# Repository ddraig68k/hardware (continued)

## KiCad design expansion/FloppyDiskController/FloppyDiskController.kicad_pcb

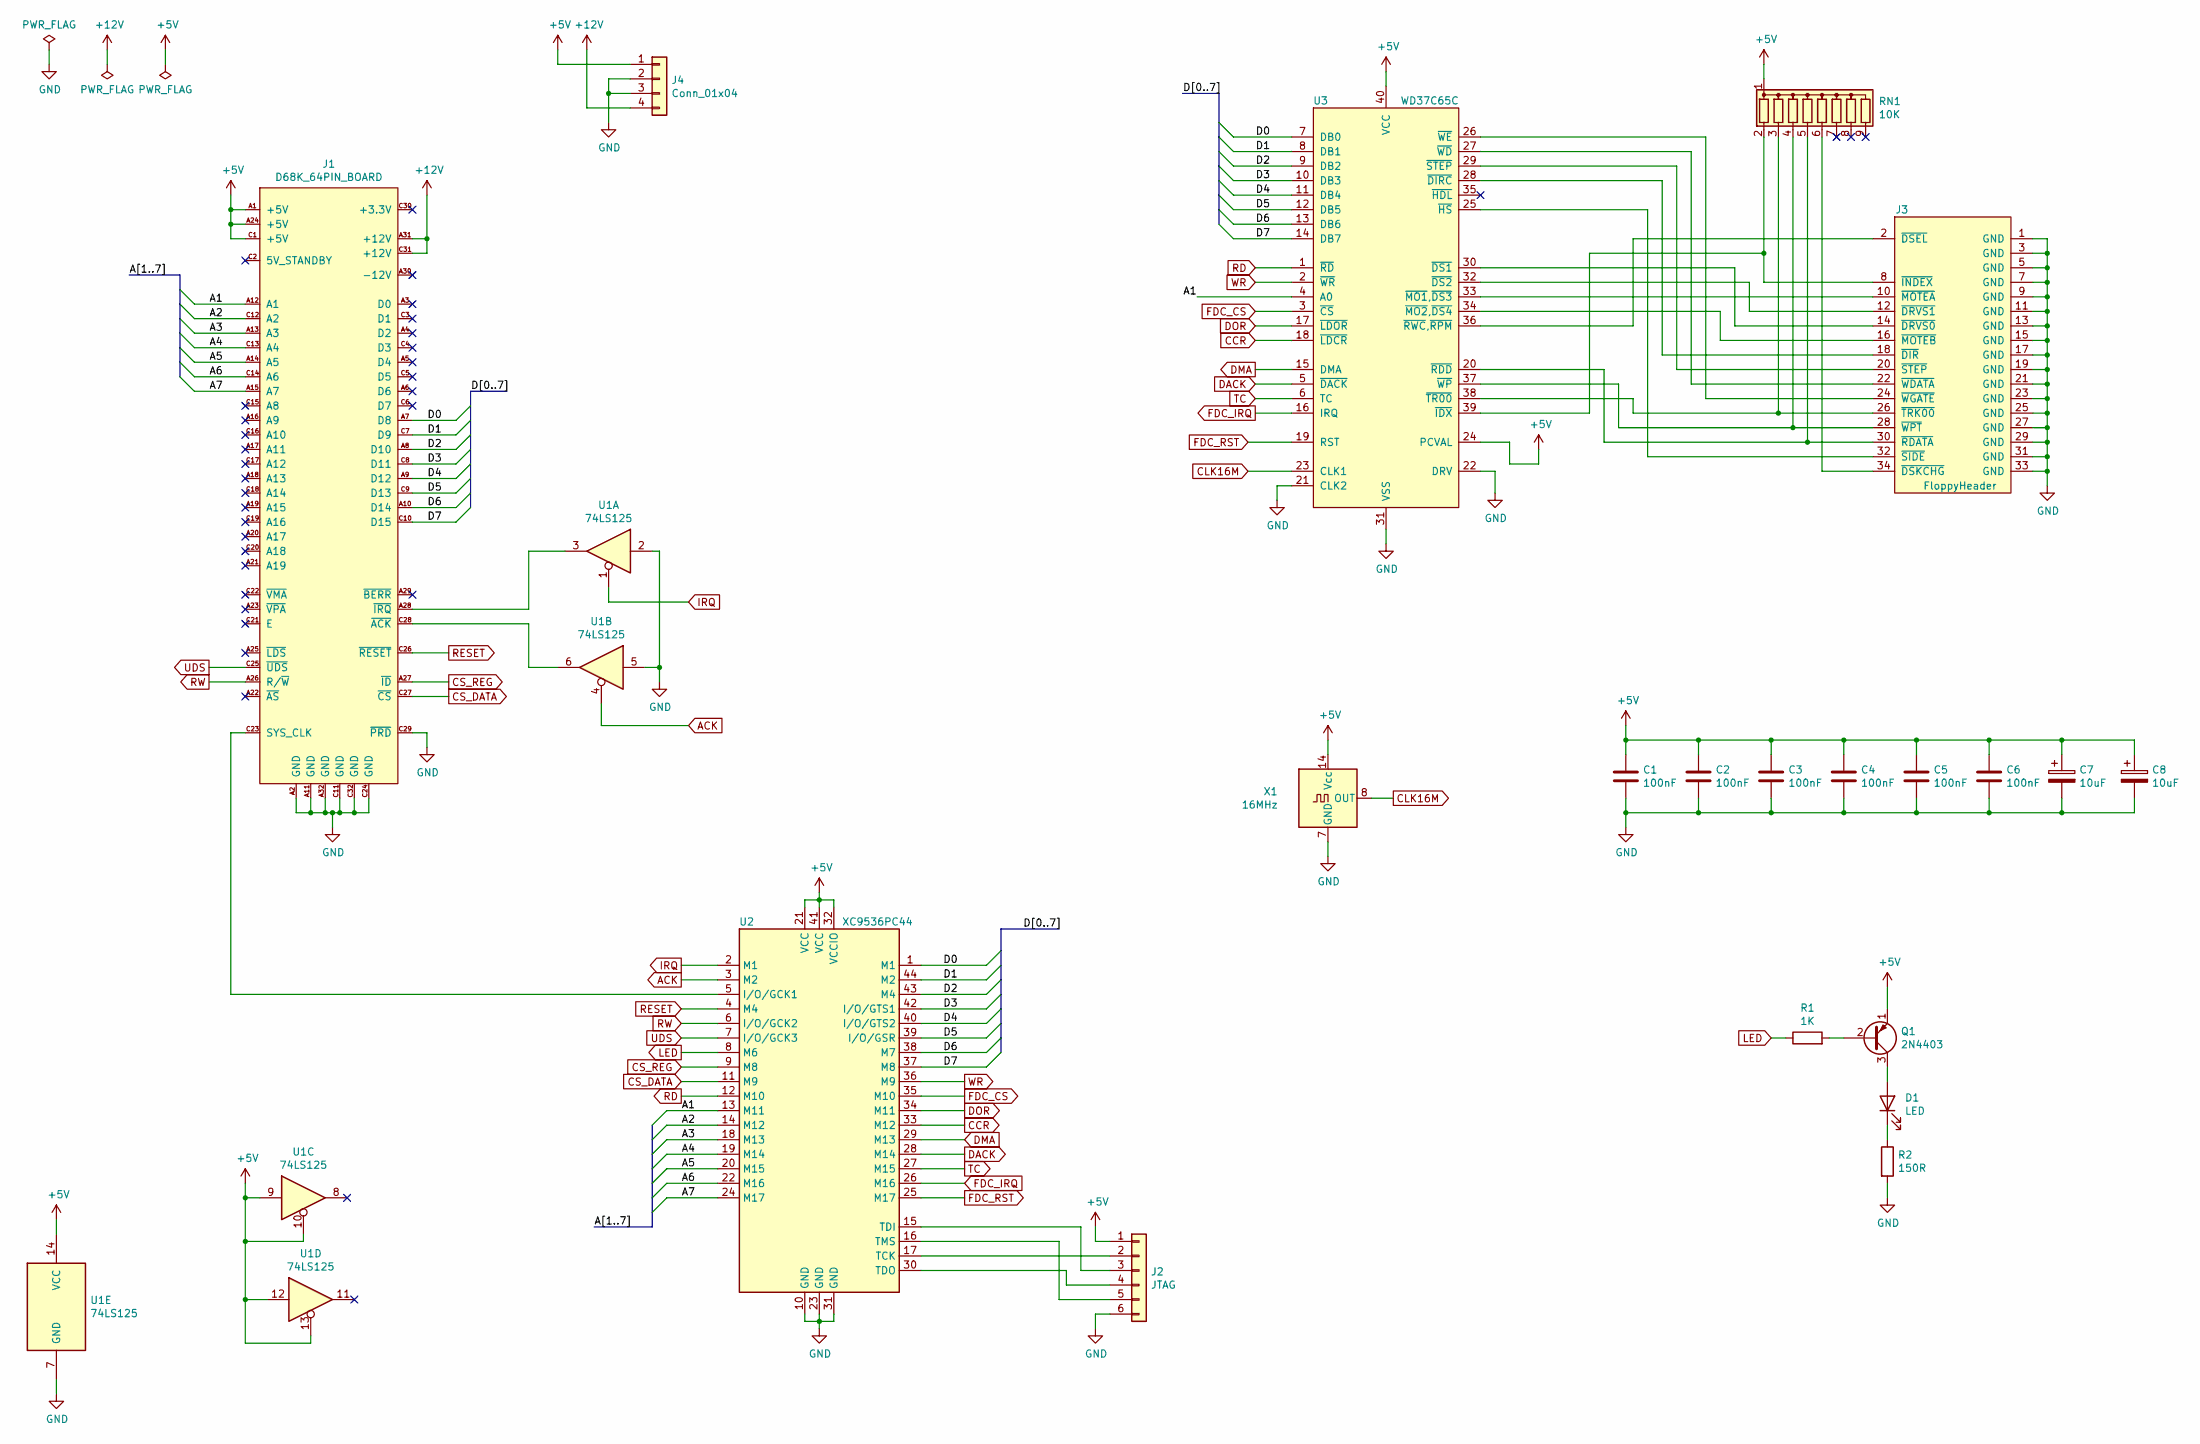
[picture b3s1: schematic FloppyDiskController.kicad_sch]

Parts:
C1, C2, C3, C4, C5, C6: 100nF; C_Disc_D3.0mm_W1.6mm_P2.50mm
C7, C8: 10uF; CP_Radial_D5.0mm_P2.50mm
D1: LED; LED_D5.0mm
J1: D68K_64PIN_BOARD; DIN41612_C_2x32_Male_Horizontal_THT
J2: JTAG; PinHeader_1x06_P2.54mm_Vertical
J3: FloppyHeader; PinHeader_2x17_P2.54mm_Vertical
J4: Conn_01x04; TE_MATE-N-LOK_350211-1_1x04_P5.08mm_Vertical
Q1: 2N4403; TO-92
R1: 1K; R_Axial_DIN0207_L6.3mm_D2.5mm_P10.16mm_Horizontal
R2: 150R; R_Axial_DIN0207_L6.3mm_D2.5mm_P10.16mm_Horizontal
RN1: 10K; R_Array_SIP9
U1: 74LS125; DIP-14_W7.62mm_Socket
U2: XC9536PC44; PLCC-44_THT-Socket
U3: WD37C65C; DIP-40_W15.24mm_Socket
X1: 16MHz; Oscillator_DIP-14

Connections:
+5V: C1.1, C2.1, C3.1, C4.1, C5.1, C6.1, C7.1, C8.1, J1.A1 (+5V), J1.A24 (+5V), J1.C1 (+5V), J2.1, J4.1, Q1.1 (E), RN1.1 (common), U1.9, U1.10, U1.12, U1.13, U1.14 (VCC), U2.21 (VCC), U2.32 (VCCIO), U2.41 (VCC), U3.24 (PCVAL), U3.40 (VCC), X1.14 (Vcc)
+12V: J1.A31 (+12V), J1.C31 (+12V), J4.4
/A1: J1.A12 (A1), U2.13 (M11), U3.4 (A0)
/A2: J1.C12 (A2), U2.14 (M12)
/A3: J1.A13 (A3), U2.18 (M13)
/A4: J1.C13 (A4), U2.19 (M14)
/A5: J1.A14 (A5), U2.20 (M15)
/A6: J1.C14 (A6), U2.22 (M16)
/A7: J1.A15 (A7), U2.24 (M17)
/D0: J1.A7 (D8), U2.1 (M1), U3.7 (DB0)
/D1: J1.C7 (D9), U2.44 (M2), U3.8 (DB1)
/D2: J1.A8 (D10), U2.43 (M4), U3.9 (DB2)
/D3: J1.C8 (D11), U2.42 (I/O/GTS1), U3.10 (DB3)
/D4: J1.A9 (D12), U2.40 (I/O/GTS2), U3.11 (DB4)
/D5: J1.C9 (D13), U2.39 (I/O/GSR), U3.12 (DB5)
/D6: J1.A10 (D14), U2.38 (M7), U3.13 (DB6)
/D7: J1.C10 (D15), U2.37 (M8), U3.14 (DB7)
ACK: U1.4, U2.3 (M2)
CCR: U2.33 (M12), U3.18 (~LDCR)
CLK16M: U3.23 (CLK1), X1.8 (OUT)
CS_DATA: J1.C27 (~CS), U2.11 (M9)
CS_REG: J1.A27 (~ID), U2.9 (M8)
DACK: U2.28 (M14), U3.5 (~DACK)
DMA: U2.29 (M13), U3.15 (DMA)
DOR: U2.34 (M11), U3.17 (~LDOR)
FDC_CS: U2.35 (M10), U3.3 (~CS)
FDC_IRQ: U2.26 (M16), U3.16 (IRQ)
FDC_RST: U2.25 (M17), U3.19 (RST)
GND: C1.2, C2.2, C3.2, C4.2, C5.2, C6.2, C7.2, C8.2, J1.A2 (GND), J1.A11 (GND), J1.A32 (GND), J1.C11 (GND), J1.C24 (GND), J1.C29 (~PRD), J1.C32 (GND), J2.6, J3.1 (GND), J3.3 (GND), J3.5 (GND), J3.7 (GND), J3.9 (GND), J3.11 (GND), J3.13 (GND), J3.15 (GND), J3.17 (GND), J3.19 (GND), J3.21 (GND), J3.23 (GND), J3.25 (GND), J3.27 (GND), J3.29 (GND), J3.31 (GND), J3.33 (GND), J4.2, J4.3, R2.2, U1.2, U1.5, U1.7 (GND), U2.10 (GND), U2.23 (GND), U2.31 (GND), U3.21 (CLK2), U3.22 (DRV), U3.31 (VSS), X1.7 (GND)
IRQ: U1.1, U2.2 (M1)
LED: R1.1, U2.8 (M6)
unnamed: D1.1 (K), R2.1
unnamed: D1.2 (A), Q1.3 (C)
unnamed: J1.A28 (~IRQ), U1.3
unnamed: J1.C23 (SYS_CLK), U2.5 (I/O/GCK1)
unnamed: J1.C28 (~ACK), U1.6
unnamed: J2.2, U2.17 (TCK)
unnamed: J2.3, U2.15 (TDI)
unnamed: J2.4, U2.30 (TDO)
unnamed: J2.5, U2.16 (TMS)
unnamed: J3.2 (~DSEL), U3.36 (~RWC,~RPM)
unnamed: J3.8 (~INDEX), RN1.2 (R1), U3.39 (~IDX)
unnamed: J3.10 (~MOTEA), U3.33 (~MO1,~DS3)
unnamed: J3.12 (~DRVS1), U3.32 (~DS2)
unnamed: J3.14 (~DRVS0), U3.30 (~DS1)
unnamed: J3.16 (~MOTEB), U3.34 (~MO2,~DS4)
unnamed: J3.18 (~DIR), U3.28 (~DIRC)
unnamed: J3.20 (~STEP), U3.29 (~STEP)
unnamed: J3.22 (~WDATA), U3.27 (~WD)
unnamed: J3.24 (~WGATE), U3.26 (~WE)
unnamed: J3.26 (~TRK00), RN1.3 (R2), U3.38 (~TR00)
unnamed: J3.28 (~WPT), RN1.4 (R3), U3.37 (~WP)
unnamed: J3.30 (~RDATA), RN1.5 (R4), U3.20 (~RDD)
unnamed: J3.32 (~SIDE), U3.25 (~HS)
unnamed: J3.34 (~DSKCHG), RN1.6 (R5)
unnamed: Q1.2 (B), R1.2
RD: U2.12 (M10), U3.1 (~RD)
RESET: J1.C26 (~RESET), U2.4 (M4)
RW: J1.A26 (R/~W), U2.6 (I/O/GCK2)
TC: U2.27 (M15), U3.6 (TC)
UDS: J1.C25 (~UDS), U2.7 (I/O/GCK3)
WR: U2.36 (M9), U3.2 (~WR)

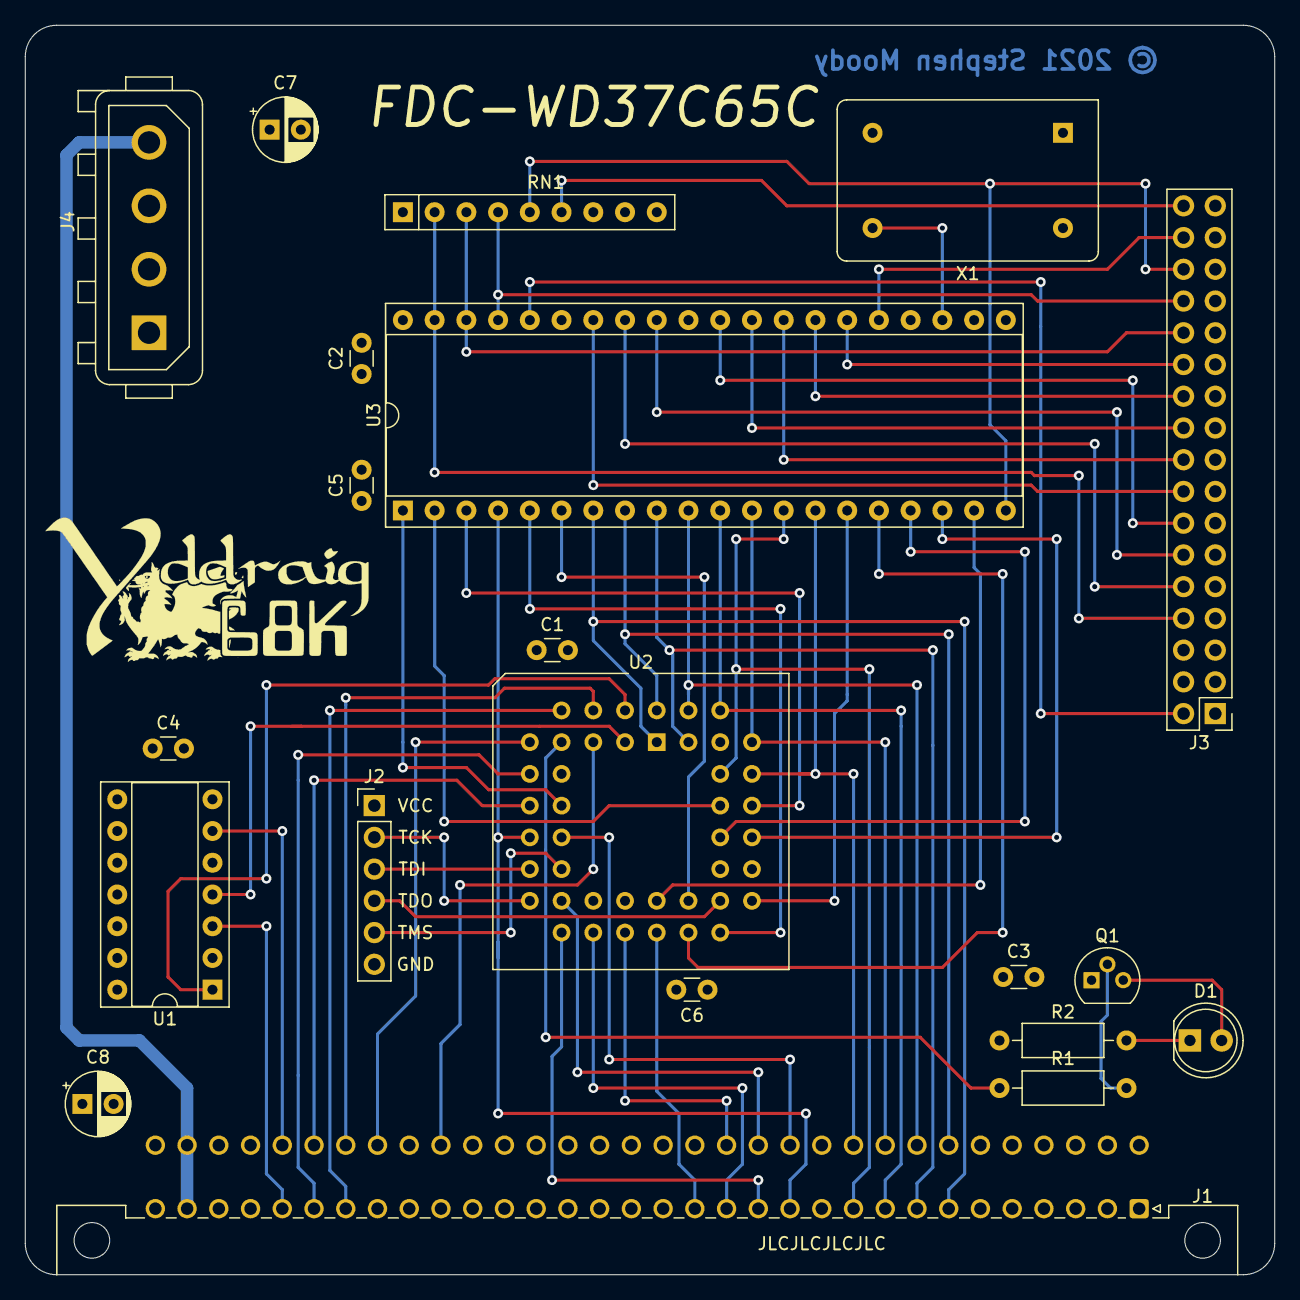
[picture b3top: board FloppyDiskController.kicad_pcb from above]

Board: 4 copper layers, 100.0 x 100.0 mm, 21 parts (0 on the bottom side), 62 nets.

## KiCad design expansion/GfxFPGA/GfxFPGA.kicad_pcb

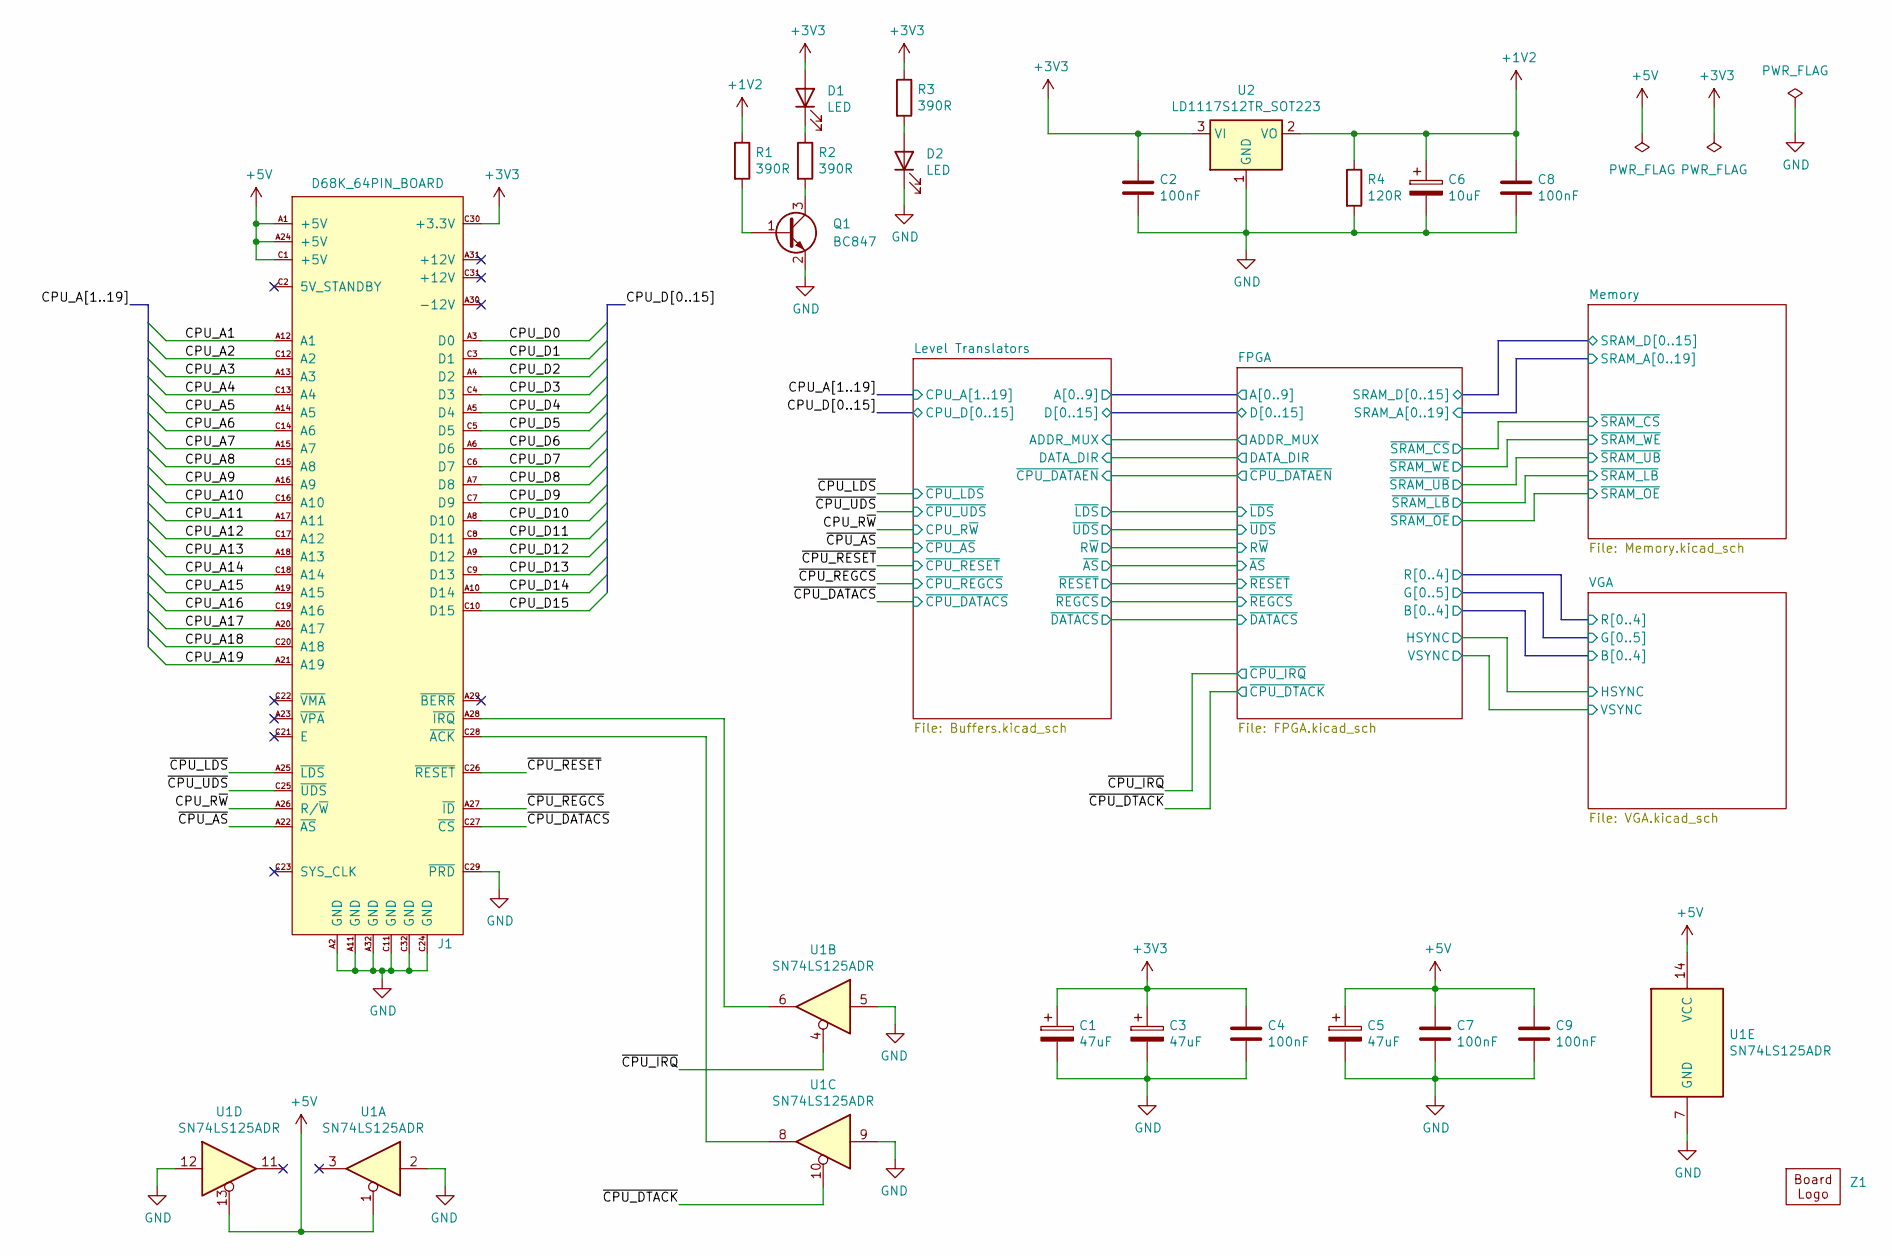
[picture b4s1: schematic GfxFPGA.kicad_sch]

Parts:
C1, C3, C5: 47uF; CP_Elec_4x5.3
C2, C4, C7, C8, C9: 100nF; C_0805_2012Metric
C6: 10uF; CP_Elec_4x5.3
D1, D2: LED; LED_1206_3216Metric
J1: D68K_64PIN_BOARD; DIN41612_C_2x32_Male_Horizontal_THT
Q1: BC847; SOT-23
R1, R2, R3: 390R; R_0805_2012Metric
R4: 120R; R_0805_2012Metric
U1: SN74LS125ADR; SO-14_3.9x8.65mm_P1.27mm
U2: LD1117S12TR_SOT223; SOT-223-3_TabPin2
Z1: Ddraig68k-26mm

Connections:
+1V2: C6.1, C8.1, R1.1, R4.1, U2.2 (VO); also elsewhere on the board
+3V3: C1.1, C2.1, C3.1, C4.1, D1.2 (A), J1.C30 (+3.3V), R3.1, U2.3 (VI); also elsewhere on the board
+5V: C5.1, C7.1, C9.1, J1.A1 (+5V), J1.A24 (+5V), J1.C1 (+5V), U1.1, U1.13, U1.14 (VCC); also elsewhere on the board
/CPU_A1: J1.A12 (A1); also elsewhere on the board
/CPU_A2: J1.C12 (A2); also elsewhere on the board
/CPU_A3: J1.A13 (A3); also elsewhere on the board
/CPU_A4: J1.C13 (A4); also elsewhere on the board
/CPU_A5: J1.A14 (A5); also elsewhere on the board
/CPU_A6: J1.C14 (A6); also elsewhere on the board
/CPU_A7: J1.A15 (A7); also elsewhere on the board
/CPU_A8: J1.C15 (A8); also elsewhere on the board
/CPU_A9: J1.A16 (A9); also elsewhere on the board
/CPU_A10: J1.C16 (A10); also elsewhere on the board
/CPU_A11: J1.A17 (A11); also elsewhere on the board
/CPU_A12: J1.C17 (A12); also elsewhere on the board
/CPU_A13: J1.A18 (A13); also elsewhere on the board
/CPU_A14: J1.C18 (A14); also elsewhere on the board
/CPU_A15: J1.A19 (A15); also elsewhere on the board
/CPU_A16: J1.C19 (A16); also elsewhere on the board
/CPU_A17: J1.A20 (A17); also elsewhere on the board
/CPU_A18: J1.C20 (A18); also elsewhere on the board
/CPU_A19: J1.A21 (A19); also elsewhere on the board
/CPU_D0: J1.A3 (D0); also elsewhere on the board
/CPU_D1: J1.C3 (D1); also elsewhere on the board
/CPU_D2: J1.A4 (D2); also elsewhere on the board
/CPU_D3: J1.C4 (D3); also elsewhere on the board
/CPU_D4: J1.A5 (D4); also elsewhere on the board
/CPU_D5: J1.C5 (D5); also elsewhere on the board
/CPU_D6: J1.A6 (D6); also elsewhere on the board
/CPU_D7: J1.C6 (D7); also elsewhere on the board
/CPU_D8: J1.A7 (D8); also elsewhere on the board
/CPU_D9: J1.C7 (D9); also elsewhere on the board
/CPU_D10: J1.A8 (D10); also elsewhere on the board
/CPU_D11: J1.C8 (D11); also elsewhere on the board
/CPU_D12: J1.A9 (D12); also elsewhere on the board
/CPU_D13: J1.C9 (D13); also elsewhere on the board
/CPU_D14: J1.A10 (D14); also elsewhere on the board
/CPU_D15: J1.C10 (D15); also elsewhere on the board
/CPU_R~W: J1.A26 (R/~W); also elsewhere on the board
/~CPU_AS: J1.A22 (~AS); also elsewhere on the board
/~CPU_DATACS: J1.C27 (~CS); also elsewhere on the board
/~CPU_DTACK: U1.10; also elsewhere on the board
/~CPU_IRQ: U1.4; also elsewhere on the board
/~CPU_LDS: J1.A25 (~LDS); also elsewhere on the board
/~CPU_REGCS: J1.A27 (~ID); also elsewhere on the board
/~CPU_RESET: J1.C26 (~RESET); also elsewhere on the board
/~CPU_UDS: J1.C25 (~UDS); also elsewhere on the board
GND: C1.2, C2.2, C3.2, C4.2, C5.2, C6.2, C7.2, C8.2, C9.2, D2.1 (K), J1.A2 (GND), J1.A11 (GND), J1.A32 (GND), J1.C11 (GND), J1.C24 (GND), J1.C29 (~PRD), J1.C32 (GND), Q1.2 (E), R4.2, U1.2, U1.5, U1.7 (GND), U1.9, U1.12, U2.1 (GND); also elsewhere on the board
unnamed: D1.1 (K), R2.1
unnamed: D2.2 (A), R3.2
unnamed: J1.C28 (~ACK), U1.8
unnamed: J1.A28 (~IRQ), U1.6
unnamed: Q1.1 (B), R1.2
unnamed: Q1.3 (C), R2.2

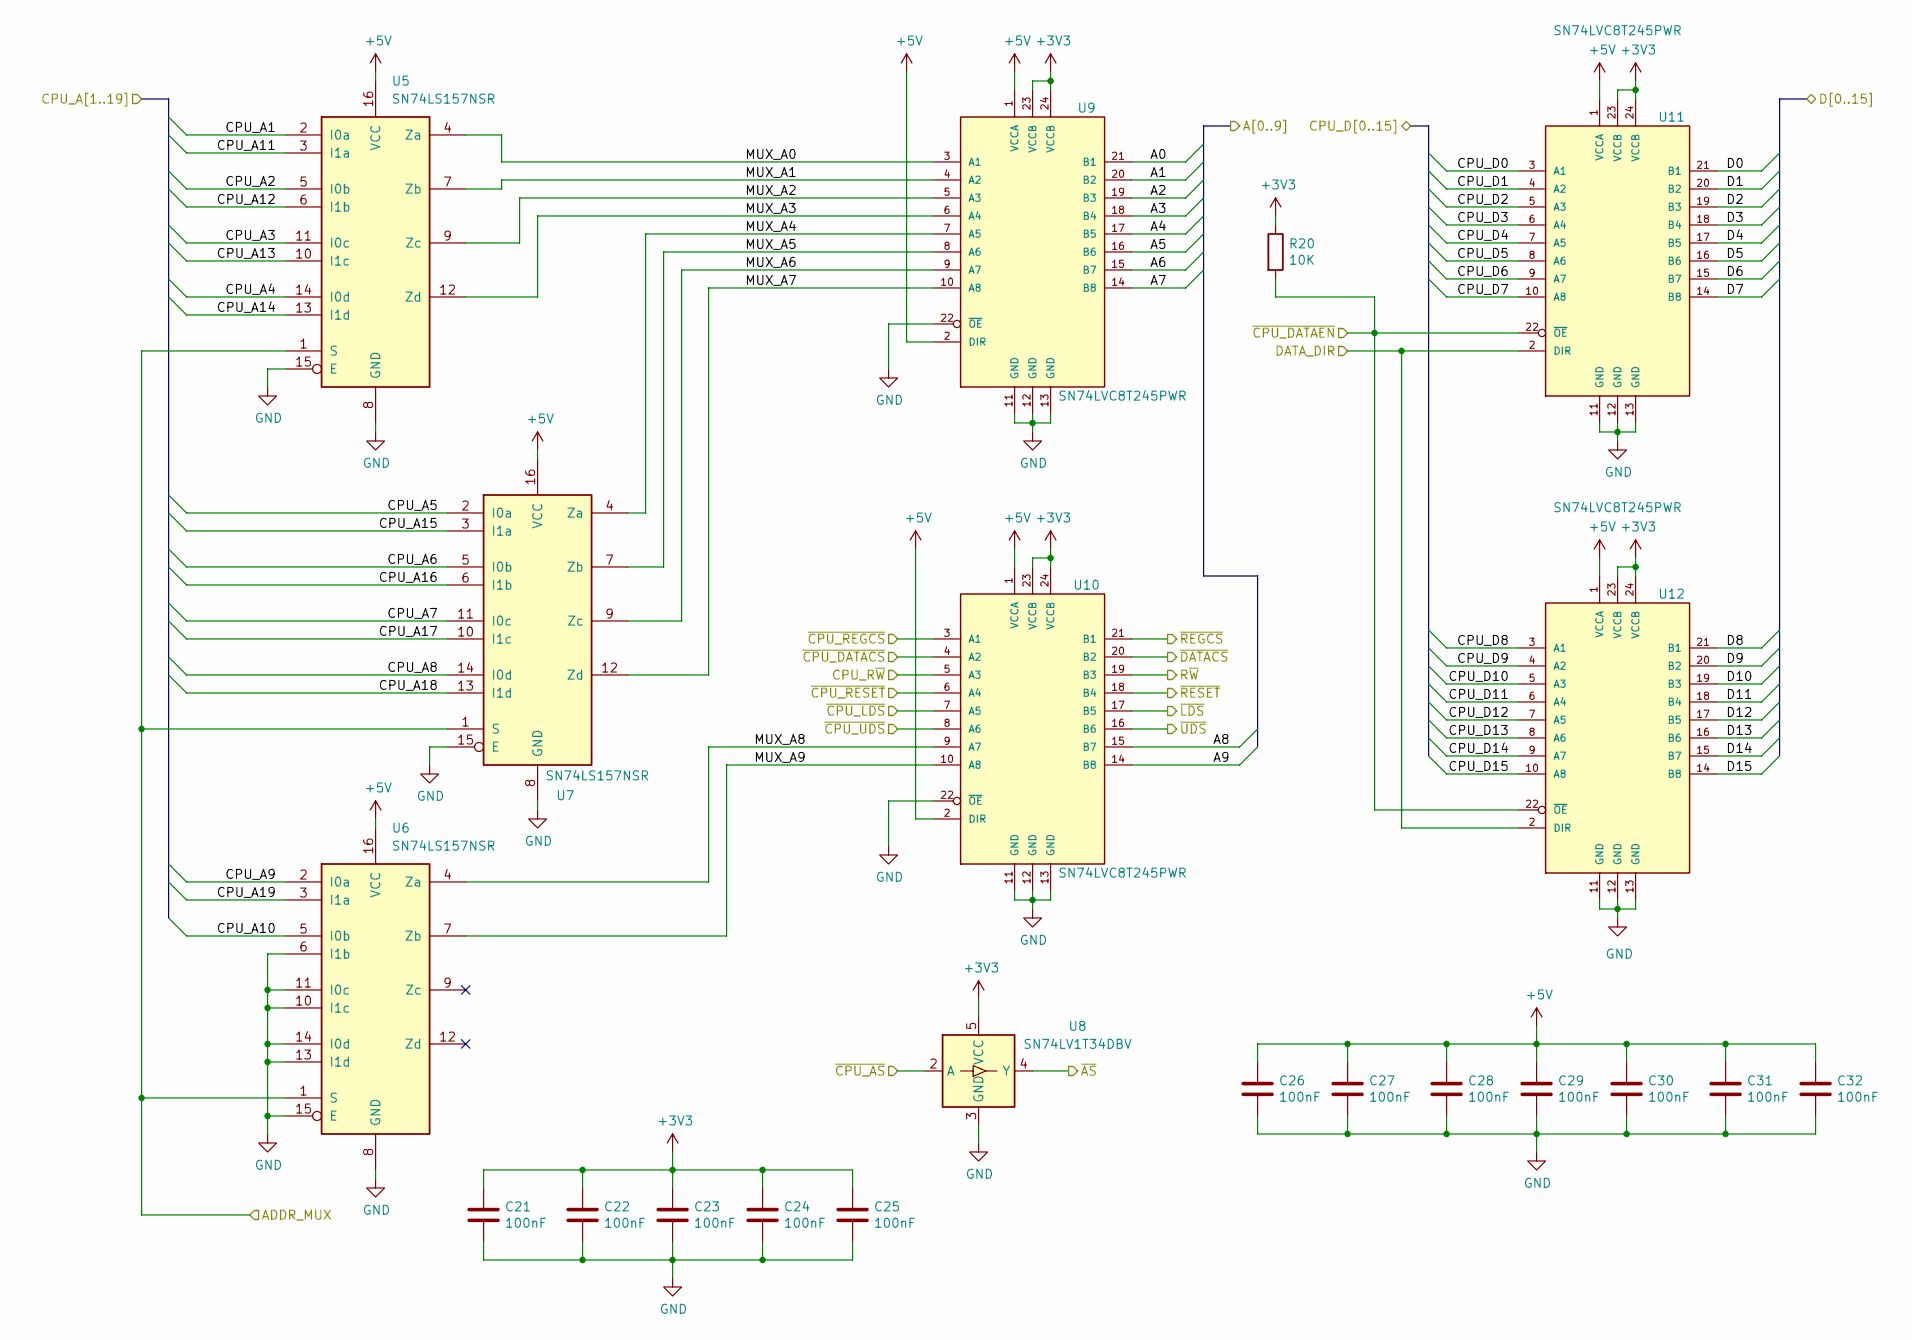
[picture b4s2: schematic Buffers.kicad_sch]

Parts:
C21, C22, C23, C24, C25, C26, C27, C28, C29, C30, C31, C32: 100nF; C_0805_2012Metric
R20: 10K; R_0805_2012Metric
U5, U6, U7: SN74LS157NSR; SO-16_5.3x10.2mm_P1.27mm
U8: SN74LV1T34DBV; SOT-23-5
U9, U10, U11, U12: SN74LVC8T245PWR; SOP65P640X120-24N

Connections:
+3V3: C21.1, C22.1, C23.1, C24.1, C25.1, R20.1, U8.5 (VCC), U9.23 (VCCB), U9.24 (VCCB), U10.23 (VCCB), U10.24 (VCCB), U11.23 (VCCB), U11.24 (VCCB), U12.23 (VCCB), U12.24 (VCCB); also elsewhere on the board
+5V: C26.1, C27.1, C28.1, C29.1, C30.1, C31.1, C32.1, U5.16 (VCC), U6.16 (VCC), U7.16 (VCC), U9.1 (VCCA), U9.2 (DIR), U10.1 (VCCA), U10.2 (DIR), U11.1 (VCCA), U12.1 (VCCA); also elsewhere on the board
/CPU_A1: U5.2 (I0a); also elsewhere on the board
/CPU_A2: U5.5 (I0b); also elsewhere on the board
/CPU_A3: U5.11 (I0c); also elsewhere on the board
/CPU_A4: U5.14 (I0d); also elsewhere on the board
/CPU_A5: U7.2 (I0a); also elsewhere on the board
/CPU_A6: U7.5 (I0b); also elsewhere on the board
/CPU_A7: U7.11 (I0c); also elsewhere on the board
/CPU_A8: U7.14 (I0d); also elsewhere on the board
/CPU_A9: U6.2 (I0a); also elsewhere on the board
/CPU_A10: U6.5 (I0b); also elsewhere on the board
/CPU_A11: U5.3 (I1a); also elsewhere on the board
/CPU_A12: U5.6 (I1b); also elsewhere on the board
/CPU_A13: U5.10 (I1c); also elsewhere on the board
/CPU_A14: U5.13 (I1d); also elsewhere on the board
/CPU_A15: U7.3 (I1a); also elsewhere on the board
/CPU_A16: U7.6 (I1b); also elsewhere on the board
/CPU_A17: U7.10 (I1c); also elsewhere on the board
/CPU_A18: U7.13 (I1d); also elsewhere on the board
/CPU_A19: U6.3 (I1a); also elsewhere on the board
/CPU_D0: U11.3 (A1); also elsewhere on the board
/CPU_D1: U11.4 (A2); also elsewhere on the board
/CPU_D2: U11.5 (A3); also elsewhere on the board
/CPU_D3: U11.6 (A4); also elsewhere on the board
/CPU_D4: U11.7 (A5); also elsewhere on the board
/CPU_D5: U11.8 (A6); also elsewhere on the board
/CPU_D6: U11.9 (A7); also elsewhere on the board
/CPU_D7: U11.10 (A8); also elsewhere on the board
/CPU_D8: U12.3 (A1); also elsewhere on the board
/CPU_D9: U12.4 (A2); also elsewhere on the board
/CPU_D10: U12.5 (A3); also elsewhere on the board
/CPU_D11: U12.6 (A4); also elsewhere on the board
/CPU_D12: U12.7 (A5); also elsewhere on the board
/CPU_D13: U12.8 (A6); also elsewhere on the board
/CPU_D14: U12.9 (A7); also elsewhere on the board
/CPU_D15: U12.10 (A8); also elsewhere on the board
/CPU_R~W: U10.5 (A3); also elsewhere on the board
/FPGA/A0: U9.21 (B1); also elsewhere on the board
/FPGA/A1: U9.20 (B2); also elsewhere on the board
/FPGA/A2: U9.19 (B3); also elsewhere on the board
/FPGA/A3: U9.18 (B4); also elsewhere on the board
/FPGA/A4: U9.17 (B5); also elsewhere on the board
/FPGA/A5: U9.16 (B6); also elsewhere on the board
/FPGA/A6: U9.15 (B7); also elsewhere on the board
/FPGA/A7: U9.14 (B8); also elsewhere on the board
/FPGA/A8: U10.15 (B7); also elsewhere on the board
/FPGA/A9: U10.14 (B8); also elsewhere on the board
/FPGA/ADDR_MUX: U5.1 (S), U6.1 (S), U7.1 (S); also elsewhere on the board
/FPGA/D0: U11.21 (B1); also elsewhere on the board
/FPGA/D1: U11.20 (B2); also elsewhere on the board
/FPGA/D2: U11.19 (B3); also elsewhere on the board
/FPGA/D3: U11.18 (B4); also elsewhere on the board
/FPGA/D4: U11.17 (B5); also elsewhere on the board
/FPGA/D5: U11.16 (B6); also elsewhere on the board
/FPGA/D6: U11.15 (B7); also elsewhere on the board
/FPGA/D7: U11.14 (B8); also elsewhere on the board
/FPGA/D8: U12.21 (B1); also elsewhere on the board
/FPGA/D9: U12.20 (B2); also elsewhere on the board
/FPGA/D10: U12.19 (B3); also elsewhere on the board
/FPGA/D11: U12.18 (B4); also elsewhere on the board
/FPGA/D12: U12.17 (B5); also elsewhere on the board
/FPGA/D13: U12.16 (B6); also elsewhere on the board
/FPGA/D14: U12.15 (B7); also elsewhere on the board
/FPGA/D15: U12.14 (B8); also elsewhere on the board
/FPGA/DATA_DIR: U11.2 (DIR), U12.2 (DIR); also elsewhere on the board
/FPGA/R~W: U10.19 (B3); also elsewhere on the board
/FPGA/~AS: U8.4 (Y); also elsewhere on the board
/FPGA/~CPU_DATAEN: R20.2, U11.22 (~OE), U12.22 (~OE); also elsewhere on the board
/FPGA/~DATACS: U10.20 (B2); also elsewhere on the board
/FPGA/~LDS: U10.17 (B5); also elsewhere on the board
/FPGA/~REGCS: U10.21 (B1); also elsewhere on the board
/FPGA/~RESET: U10.18 (B4); also elsewhere on the board
/FPGA/~UDS: U10.16 (B6); also elsewhere on the board
/Level Translators/MUX_A0: U5.4 (Za), U9.3 (A1)
/Level Translators/MUX_A1: U5.7 (Zb), U9.4 (A2)
/Level Translators/MUX_A2: U5.9 (Zc), U9.5 (A3)
/Level Translators/MUX_A3: U5.12 (Zd), U9.6 (A4)
/Level Translators/MUX_A4: U7.4 (Za), U9.7 (A5)
/Level Translators/MUX_A5: U7.7 (Zb), U9.8 (A6)
/Level Translators/MUX_A6: U7.9 (Zc), U9.9 (A7)
/Level Translators/MUX_A7: U7.12 (Zd), U9.10 (A8)
/Level Translators/MUX_A8: U6.4 (Za), U10.9 (A7)
/Level Translators/MUX_A9: U6.7 (Zb), U10.10 (A8)
/~CPU_AS: U8.2 (A); also elsewhere on the board
/~CPU_DATACS: U10.4 (A2); also elsewhere on the board
/~CPU_LDS: U10.7 (A5); also elsewhere on the board
/~CPU_REGCS: U10.3 (A1); also elsewhere on the board
/~CPU_RESET: U10.6 (A4); also elsewhere on the board
/~CPU_UDS: U10.8 (A6); also elsewhere on the board
GND: C21.2, C22.2, C23.2, C24.2, C25.2, C26.2, C27.2, C28.2, C29.2, C30.2, C31.2, C32.2, U5.8 (GND), U5.15 (E), U6.6 (I1b), U6.8 (GND), U6.10 (I1c), U6.11 (I0c), U6.13 (I1d), U6.14 (I0d), U6.15 (E), U7.8 (GND), U7.15 (E), U8.3 (GND), U9.11 (GND), U9.12 (GND), U9.13 (GND), U9.22 (~OE), U10.11 (GND), U10.12 (GND), U10.13 (GND), U10.22 (~OE), U11.11 (GND), U11.12 (GND), U11.13 (GND), U12.11 (GND), U12.12 (GND), U12.13 (GND); also elsewhere on the board
